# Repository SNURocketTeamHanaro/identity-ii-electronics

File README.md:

# Identity-II Electronics
Electrical hardware of data acquisition and control system of Identity-II rocket

### Specification
1. Data Acquisition
   - Altitude measurement via [BMP280](https://cdn-shop.adafruit.com/datasheets/BST-BMP280-DS001-11.pdf)
   - 3-Axis Accelerometer, 3-Axis Gyroscope, 3-Axis Magnetometer reads data in every cycle
   - System time is recorded with the data
   - All the data measurements are taken in every 5-7 ms
   - Raspberry Pi camera module saves the recorded image automatically after the power is on
1. Communication
   - Zigbee communication is tested to reach 1000m without severe interference
   - Baud rate of 38400 is used for serial communication with the XBee module; At higher rate, some Arduino chips are not able to handle the speed of the signal alternation
   - Rocket status code along with the current altitude and time is sent via Zigbee channel
1. Control
   - Drogue parachute ejection at the peak altitude; Simple peak detection
   - Main parachute ejection in two modes
     1. Relative altitude mode (Max. Alt. < 390m): Main parachute ejection at "alt. = max. alt. - 70m"
     2. Absolute altitude mode (Max. Alt. > 390m): Main parachute ejection at "alt. = 320m"
1. Others
   - Additional 6 analog pins of Arduino Micro core can be reachable at the back of the core module

### Additional Requirements
#### Hardware
- Li-Po battery 3.7V, minimum 2000 mAh (x3)
- [Buck converter 5V output, minimum 2A (x1)](https://www.amazon.com/eBoot-LM2596-Converter-3-0-40V-1-5-35V/dp/B01GJ0SC2C/ref=sr_1_1_sspa?ie=UTF8&qid=1540806963&sr=8-1-spons&keywords=buck+converter&psc=1)
- Arduino Micro (x1)
- Digi XBee-Pro (x1)
- [MicroSD card adapter (x1)](https://www.amazon.com/SenMod-Adapter-Reader-Module-Arduino/dp/B01JYNEX56/ref=sr_1_2?ie=UTF8&qid=1540804647&sr=8-2&keywords=Micro+SD+board) (You may use other boards) 
- [GY-91 IMU sensor (x1)](https://www.amazon.com/WINGONEER-MPU9250-Acceleration-Gyroscope-Compass/dp/B06XHJQKT6/ref=sr_1_1?ie=UTF8&qid=1540807315&sr=8-1&keywords=gy+91)
- L293B (x1)
- Raspberry Pi 3 or high (x1)
- PiCamera for RPi (x1)
- Power switch (x1)
- Some terminal blocks
- Some hexagonal supporters, 3-phi
#### Software
- Arduino source code ()
- Data decoder code ()

### Installation
There are three PCB layers with additional battery mount assembled in the following order:  
(top)  
battery  
power module  
core module  
imu module  
RPi Camera and Power button mount  
RPi  

### Credit
[Jaerin Lee](https://github.com/ironjr)  
Lead Electronics and Software Developer  
SNU Rocket Team Hanaro

Documented with KiCAD version 5.0.0

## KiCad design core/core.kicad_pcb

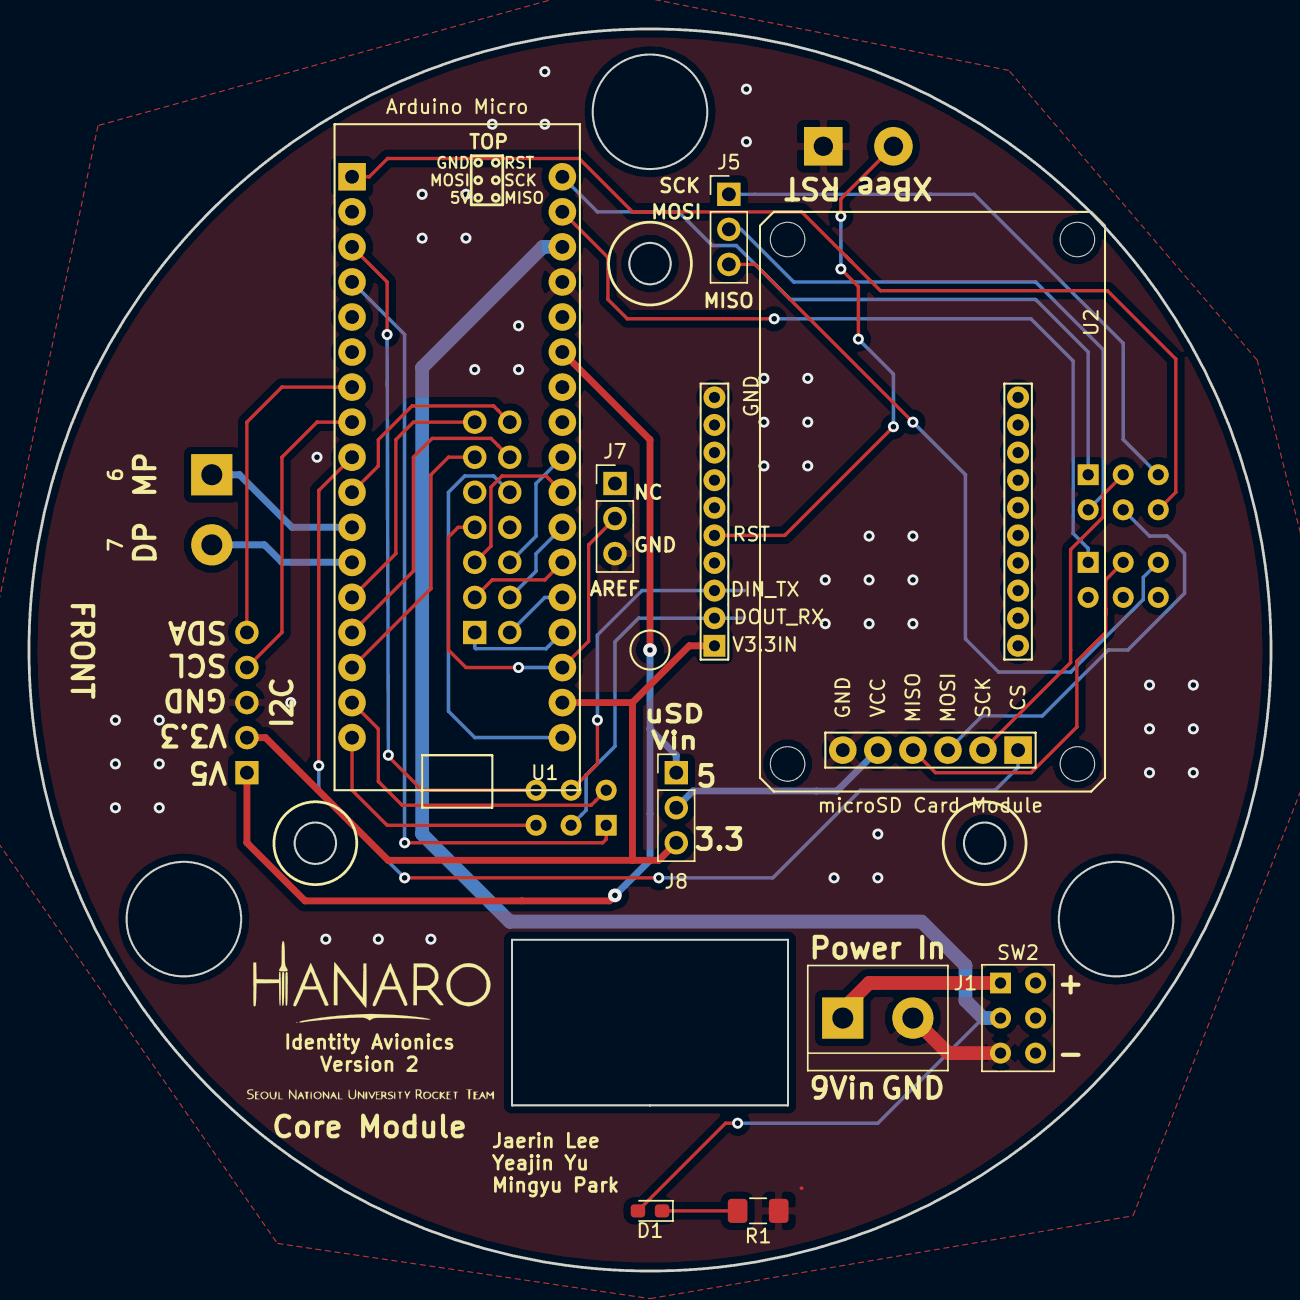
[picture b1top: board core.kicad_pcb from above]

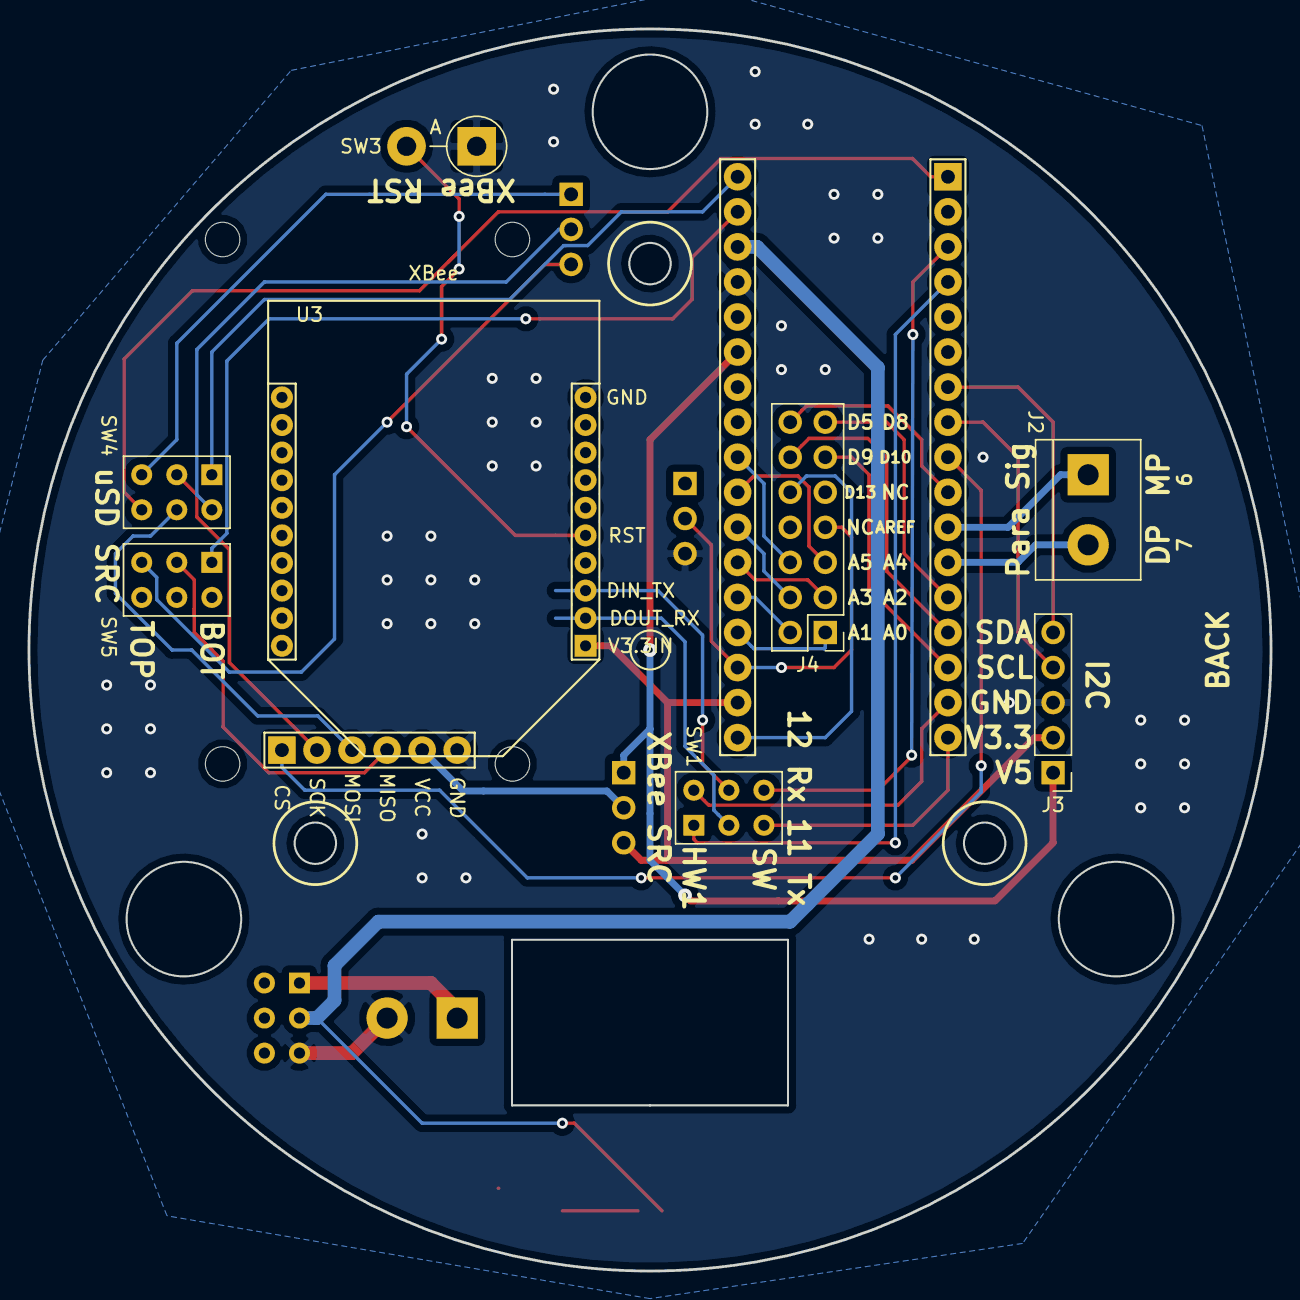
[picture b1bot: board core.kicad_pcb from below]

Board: 2 copper layers, 90.0 x 90.0 mm, 17 parts (8 on the bottom side), 40 nets.

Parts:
D1: LED; LED_0603_1608Metric_Pad1.05x0.95mm_HandSolder
J1, J2: Conn_01x02; TerminalBlock_bornier-2_P5.08mm
J3: Conn_01x05; Pin_Header_Straight_1x05_Pitch2.54mm
J4: Conn_02x07_Counter_Clockwise; Pin_Header_Straight_2x07_Pitch2.54mm
J5, J7, J8: Conn_01x03; Pin_Header_Straight_1x03_Pitch2.54mm
R1: R; R_1206_3216Metric_Pad1.42x1.75mm_HandSolder
SW1, SW4, SW5: SW_DPDT_x2; SW_NKK_G1xJP
SW2: SW_DPDT_x2 POW; SW_NKK_G1xJP
SW3: SW_Push; D_5W_P5.08mm_Vertical_AnodeUp
U1: ArduinoMicro; Arduino_Micro
U2: uSDcardDeck; uSDcard_Type_1
U3: XBeeProS1; XBee

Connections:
/3.3VOut: J3.2, J8.3, U1.19, U3.1
/5VOut: J3.1, J8.1, U1.29
/A0: J4.1, U1.21
/A1: J4.2, U1.22
/A2: J4.3, U1.23
/A3: J4.4, U1.24
/A4: J4.5, U1.25
/A5: J4.6, U1.26
/AREF: J4.7, J7.2, U1.20
/D5: J4.14, U1.10
/D8: J4.13, U1.13
/D9: J4.12, U1.14
/D10: J4.11, U1.15
/D13: J4.10, U1.18
/DROGUE: J2.2, U1.12
/GND: J1.2, J3.3, J7.3, R1.1, SW2.3, SW3.1, U1.31, U2.6, U3.10
/I2C_SCL: J3.4, U1.8
/I2C_SDA: J3.5, U1.7
/MAIN: J2.1, U1.11
/MISO_TOP: J5.3, SW5.3
/MOSI_TOP: J5.2, SW4.6
/SCK_TOP: J5.1, SW4.3
/XBee_DIN: SW1.5, U3.3
/XBee_DOUT: SW1.2, U3.2
/uSD_MISO: SW5.2, U2.4
/uSD_MOSI: SW4.5, U2.3
/uSD_SCK: SW4.2, U2.2
/uSD_VCC: J8.2, U2.5
unnamed: D1.1, R1.2
unnamed: D1.2, SW2.2, U1.32
unnamed: J1.1, SW2.1
unnamed: SW1.1, U1.4
unnamed: SW1.3, U1.17
unnamed: SW1.4, U1.3
unnamed: SW1.6, U1.16
unnamed: SW3.2, U3.5
unnamed: SW4.1, U1.34
unnamed: SW4.4, U1.1
unnamed: SW5.1, U1.33
unnamed: U1.9, U2.1

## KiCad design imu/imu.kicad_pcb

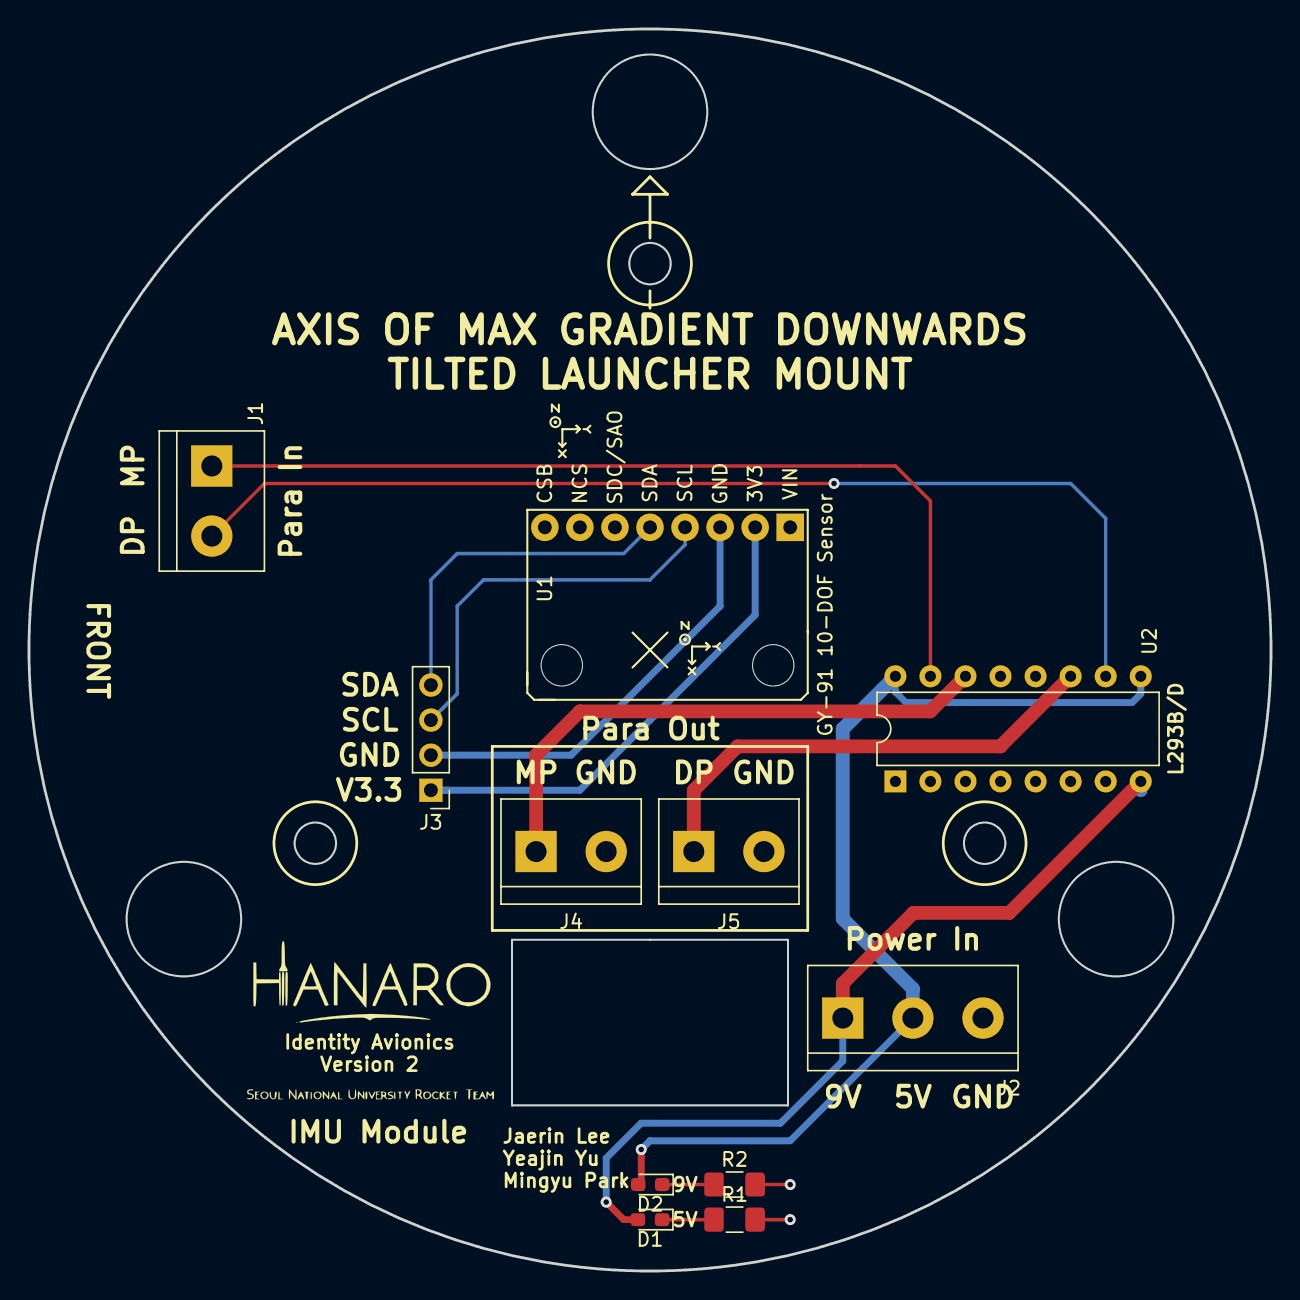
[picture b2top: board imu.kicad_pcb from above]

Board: 2 copper layers, 90.0 x 90.0 mm, 11 parts (0 on the bottom side), 13 nets.

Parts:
D1, D2: LED; LED_0603_1608Metric_Pad1.05x0.95mm_HandSolder
J1, J4, J5: Conn_01x02; TerminalBlock_bornier-2_P5.08mm
J2: Conn_01x03; TerminalBlock_bornier-3_P5.08mm
J3: Conn_01x04; PinHeader_1x04_P2.54mm_Vertical
R1, R2: R; R_1206_3216Metric_Pad1.42x1.75mm_HandSolder
U1: GY-91
U2: L293; DIP-16_W7.62mm

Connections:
/5Vin: D2.2, J2.2, U2.9, U2.16
/9Vin: D1.2, J2.1, U2.8
/DrogueIn: J1.2, U2.10
/DrogueOut: J5.1, U2.11
/GND: J2.3, J4.2, J5.2, R1.2, R2.2, U2.4, U2.5, U2.12, U2.13
/GY91_GND: J3.2, U1.3
/GY91_SCL: J3.3, U1.4
/GY91_SDA: J3.4, U1.5
/GY91_VCC: J3.1, U1.2
/MainIn: J1.1, U2.15
/MainOut: J4.1, U2.14
unnamed: D1.1, R1.1
unnamed: D2.1, R2.1

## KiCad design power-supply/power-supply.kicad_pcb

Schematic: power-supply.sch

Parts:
C1, C2, C3: CP1; CP_Radial_D10.0mm_P5.00mm
C4, C7: CP1; CP_Elec_5x5.3
C5, C9: CP1; CP_Elec_8x10
C6, C8: CP1; CP_EIA-6032-20_AVX-F_Pad2.25x2.35mm_HandSolder
D1, D2, D5, D8: D; D_5W_P10.16mm_Horizontal
D3, D4: LED; LED_0603_1608Metric_Pad1.05x0.95mm_HandSolder
J1: Conn_01x02; TerminalBlock_bornier-2_P5.08mm
J2, J3: Conn_01x03; TerminalBlock_bornier-3_P5.08mm
R1, R2: R; R_1206_3216Metric_Pad1.42x1.75mm_HandSolder
SW1: SW_DPDT_x2; SW_NKK_G1xJP
U1: BuckConv; Buck_Converter_LM2596_3A
U2: L7805; TO-220-3_Vertical
U5: L7809; TO-220-3_Vertical

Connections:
/ARD_POW: C8.1, D5.1, J2.2, U2.3 (OUT)
/RASP_POW: C5.1, C9.1, D8.1, J1.1, U1.4
/V9out: C6.1, C7.1, J2.1, U2.1 (IN), U5.3 (OUT)
GND: C1.2, C2.2, C3.2, C4.2, C5.2, C6.2, C7.2, C8.2, C9.2, D1.2, D2.2, D3.1, D4.1, D5.2, D8.2, J1.2, J2.3, J3.3, SW1.3 (C), SW1.4 (A), U1.2, U1.3, U2.2 (GND), U5.2 (GND)
unnamed: C1.1, C3.1, D1.1, R1.1, SW1.2 (B), U1.1
unnamed: C2.1, C4.1, D2.1, R2.2, SW1.5 (B), U5.1 (IN)
unnamed: D3.2, R1.2
unnamed: D4.2, R2.1
VDD: J3.2, SW1.1 (A)
VSS: J3.1, SW1.6 (C)

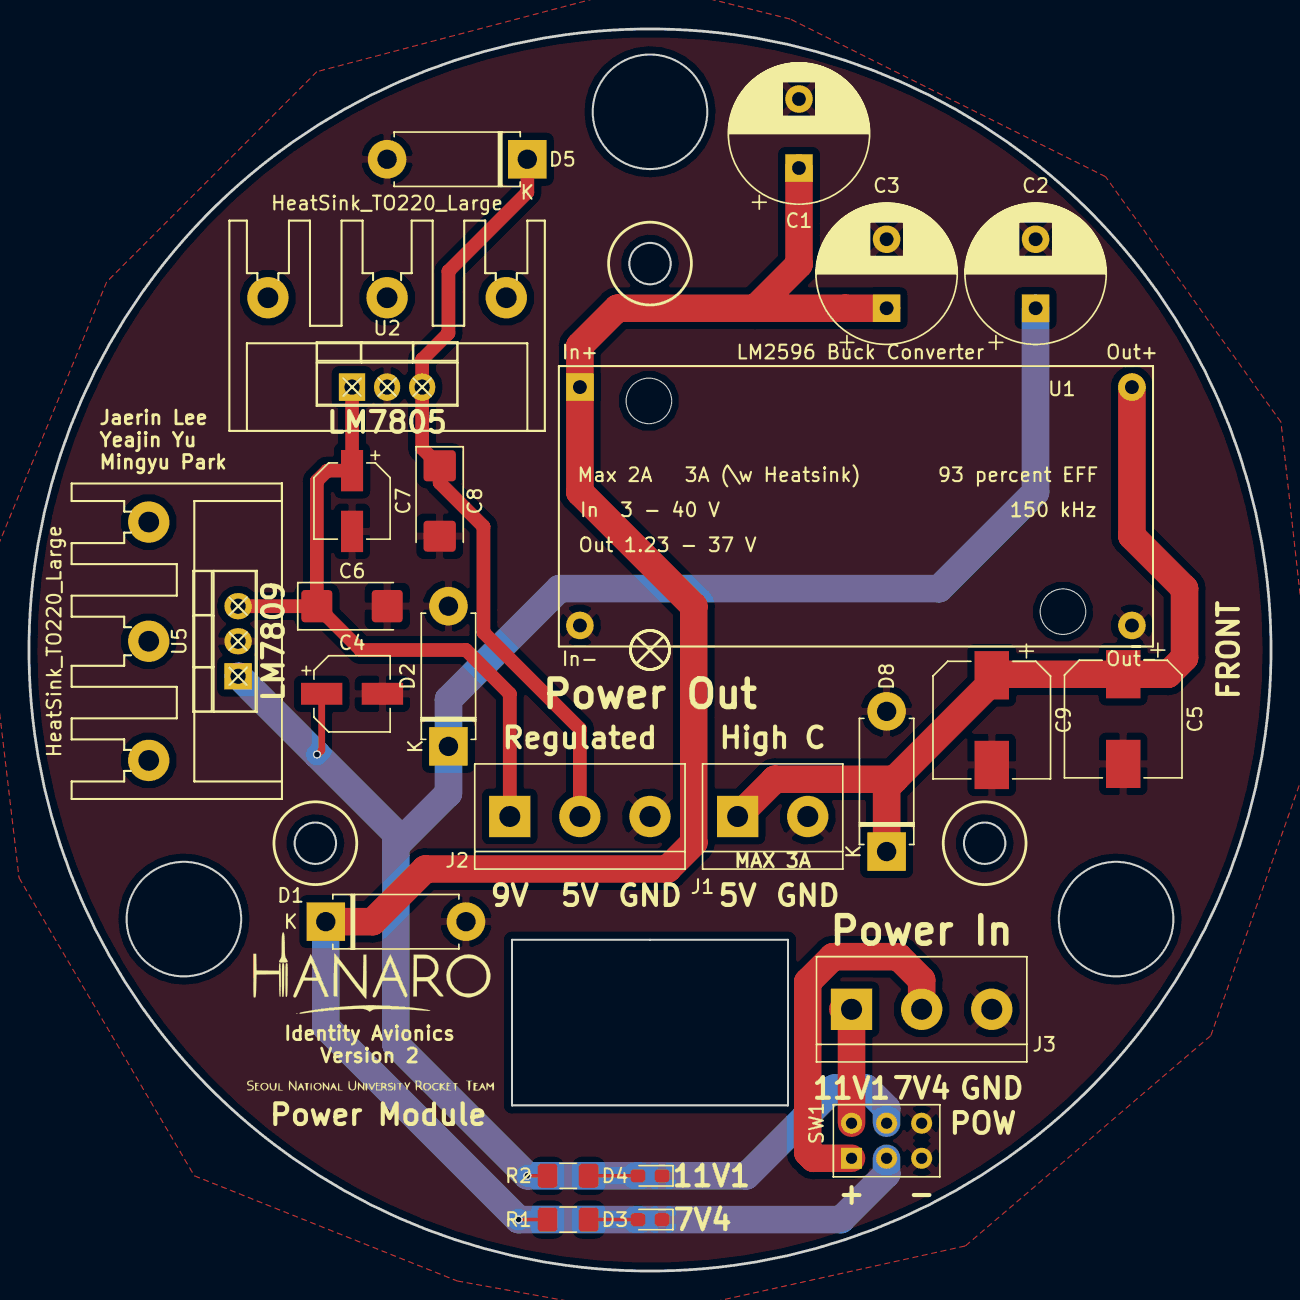
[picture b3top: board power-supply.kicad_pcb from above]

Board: 2 copper layers, 90.0 x 90.0 mm, 24 parts (0 on the bottom side), 10 nets.

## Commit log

2018-10-29 Add KiCAD project files
2019-01-12 added old legacy
